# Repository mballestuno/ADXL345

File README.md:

# ADXL345
Using Arduino with this Digital Accelerometer integrated PCB

Files in the project

-Eagle Files
-Examples with arduino

Los acelerómetros son transductores de entrada que captan la información de una magnitud física como es la aceleración. Muy utilizados podemos tenernos incorporados en nuestros Smartphone o cuando jugamos a la WII, para medir la actividad e inactividad con nuestro cuerpo así como una posible caída .
El ADXL345 es un acelerómetro digital de 3 ejes de Analog Devices. Algunas de sus características son que tiene bajo consumo, es pequeño y tiene una alta resolución de 13 bits y se comunica a través de SPI o I2C con otros dispositivos como un microcontrolador.
En el taller construiremos la placa de expansión de Sparkfun [2] con todo lo necesario para su conexión con otros dispositivos y perfectamente serigrafiado. Puedes verla en https://www.sparkfun.com/products/9836. Nosotros lo construiremos por 2 por lo que podrás ahorrarte un 90% eso sumado a que se aprenderá su funcionamiento y la satisfacción de haberlo realizado utilizando un horno de reflujo y desentrañando la tecnología SMD

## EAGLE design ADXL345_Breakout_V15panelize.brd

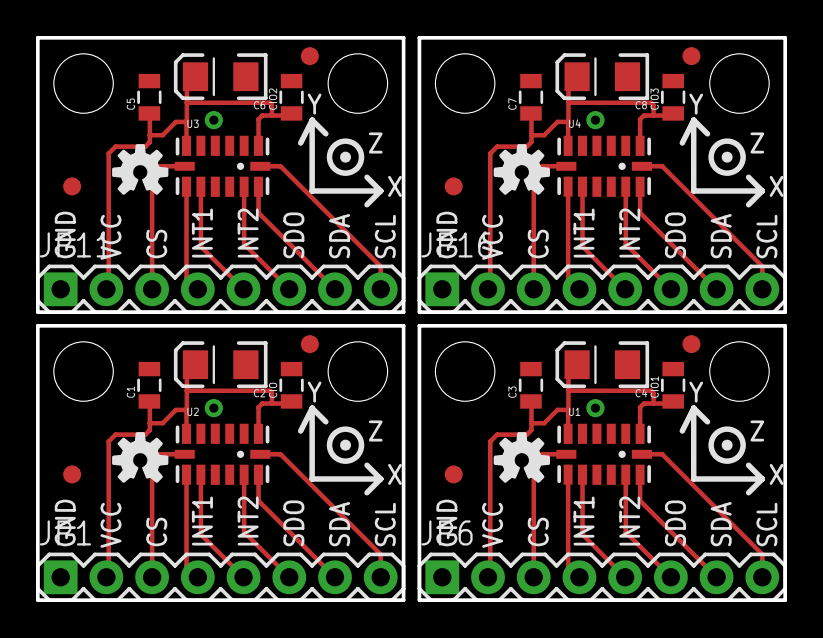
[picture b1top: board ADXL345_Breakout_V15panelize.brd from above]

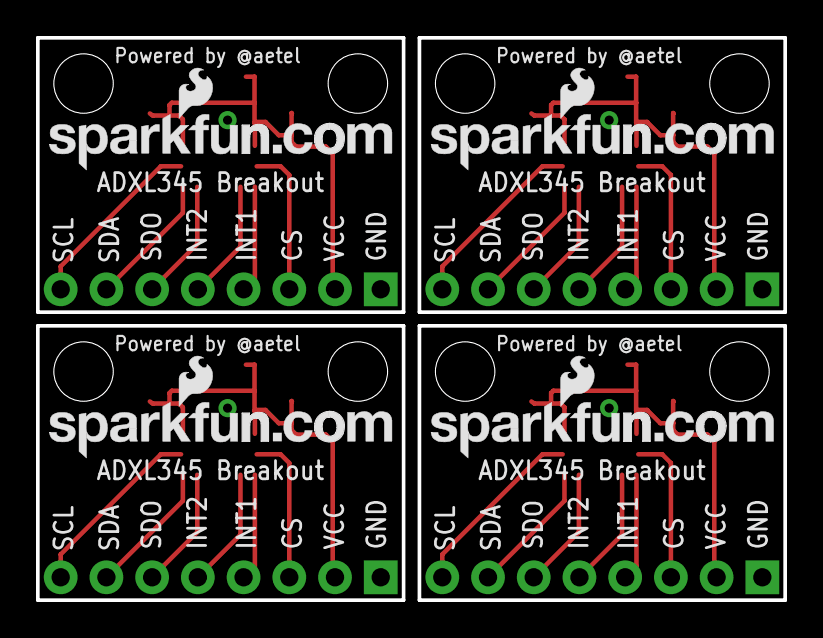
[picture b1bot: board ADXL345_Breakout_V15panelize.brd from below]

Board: 2 copper layers, 41.5 x 31.2 mm, 44 parts (4 on the bottom side), 32 nets.

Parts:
C1, C3, C5, C7: 0.1uF; 0805
C2, C4, C6, C8: 10uF; EIA3216
CIO, CIO1, CIO2, CIO3: 0.1uF; 0805
JP1, JP6, JP11, JP16: 1X08
JP2, JP3, JP7, JP8, JP12, JP13, JP17, JP18: STAND-OFF
JP4, JP5, JP9, JP10, JP14, JP15, JP19, JP20: FIDUCIAL1X2; FIDUCIAL-1X2
U1, U2, U3, U4: ADXL345PATRICK; LGA14_1:1_PATRICK
U$1, U$2, U$5, U$7: LOGO-SFENEW; SFE-NEW-WEBLOGO
U$3, U$4, U$6, U$8: OSHW-LOGOS; OSHW-LOGO-S

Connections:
CS: JP1.3, U2.7
CS1: JP6.3, U1.7
CS2: JP11.3, U3.7
CS3: JP16.3, U4.7
GND: C1.2, C2.C, CIO.2, JP1.1, U2.2, U2.4, U2.5
GND1: C3.2, C4.C, CIO1.2, JP6.1, U1.2, U1.4, U1.5
GND2: C5.2, C6.C, CIO2.2, JP11.1, U3.2, U3.4, U3.5
GND3: C7.2, C8.C, CIO3.2, JP16.1, U4.2, U4.4, U4.5
INT1: JP1.4, U2.8
INT2: JP1.5, U2.9
INT3: JP6.5, U1.9
INT4: JP6.4, U1.8
INT5: JP11.5, U3.9
INT6: JP11.4, U3.8
INT7: JP16.5, U4.9
INT8: JP16.4, U4.8
SCL: JP1.8, U2.14
SCL1: JP6.8, U1.14
SCL2: JP11.8, U3.14
SCL3: JP16.8, U4.14
SDA: JP1.7, U2.13
SDA1: JP6.7, U1.13
SDA2: JP11.7, U3.13
SDA3: JP16.7, U4.13
SDO: JP1.6, U2.12
SDO1: JP6.6, U1.12
SDO2: JP11.6, U3.12
SDO3: JP16.6, U4.12
VCC: C1.1, C2.A, CIO.1, JP1.2, U2.1, U2.6
VCC1: C3.1, C4.A, CIO1.1, JP6.2, U1.1, U1.6
VCC2: C5.1, C6.A, CIO2.1, JP11.2, U3.1, U3.6
VCC3: C7.1, C8.A, CIO3.1, JP16.2, U4.1, U4.6

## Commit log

2015-08-24 Cambios tontos
    Cambios tontos
2015-08-24 Prueba
2015-10-12 Creación del proyecto de Taller
2016-03-21 Incluidos los archivos gerber
2016-03-21 Actualización gitignore

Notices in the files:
parts and their libraries:
SparkFun-Aesthetics: Licensing: CC v3.0 Share-Alike You are welcome to use this library for commercial purposes.
